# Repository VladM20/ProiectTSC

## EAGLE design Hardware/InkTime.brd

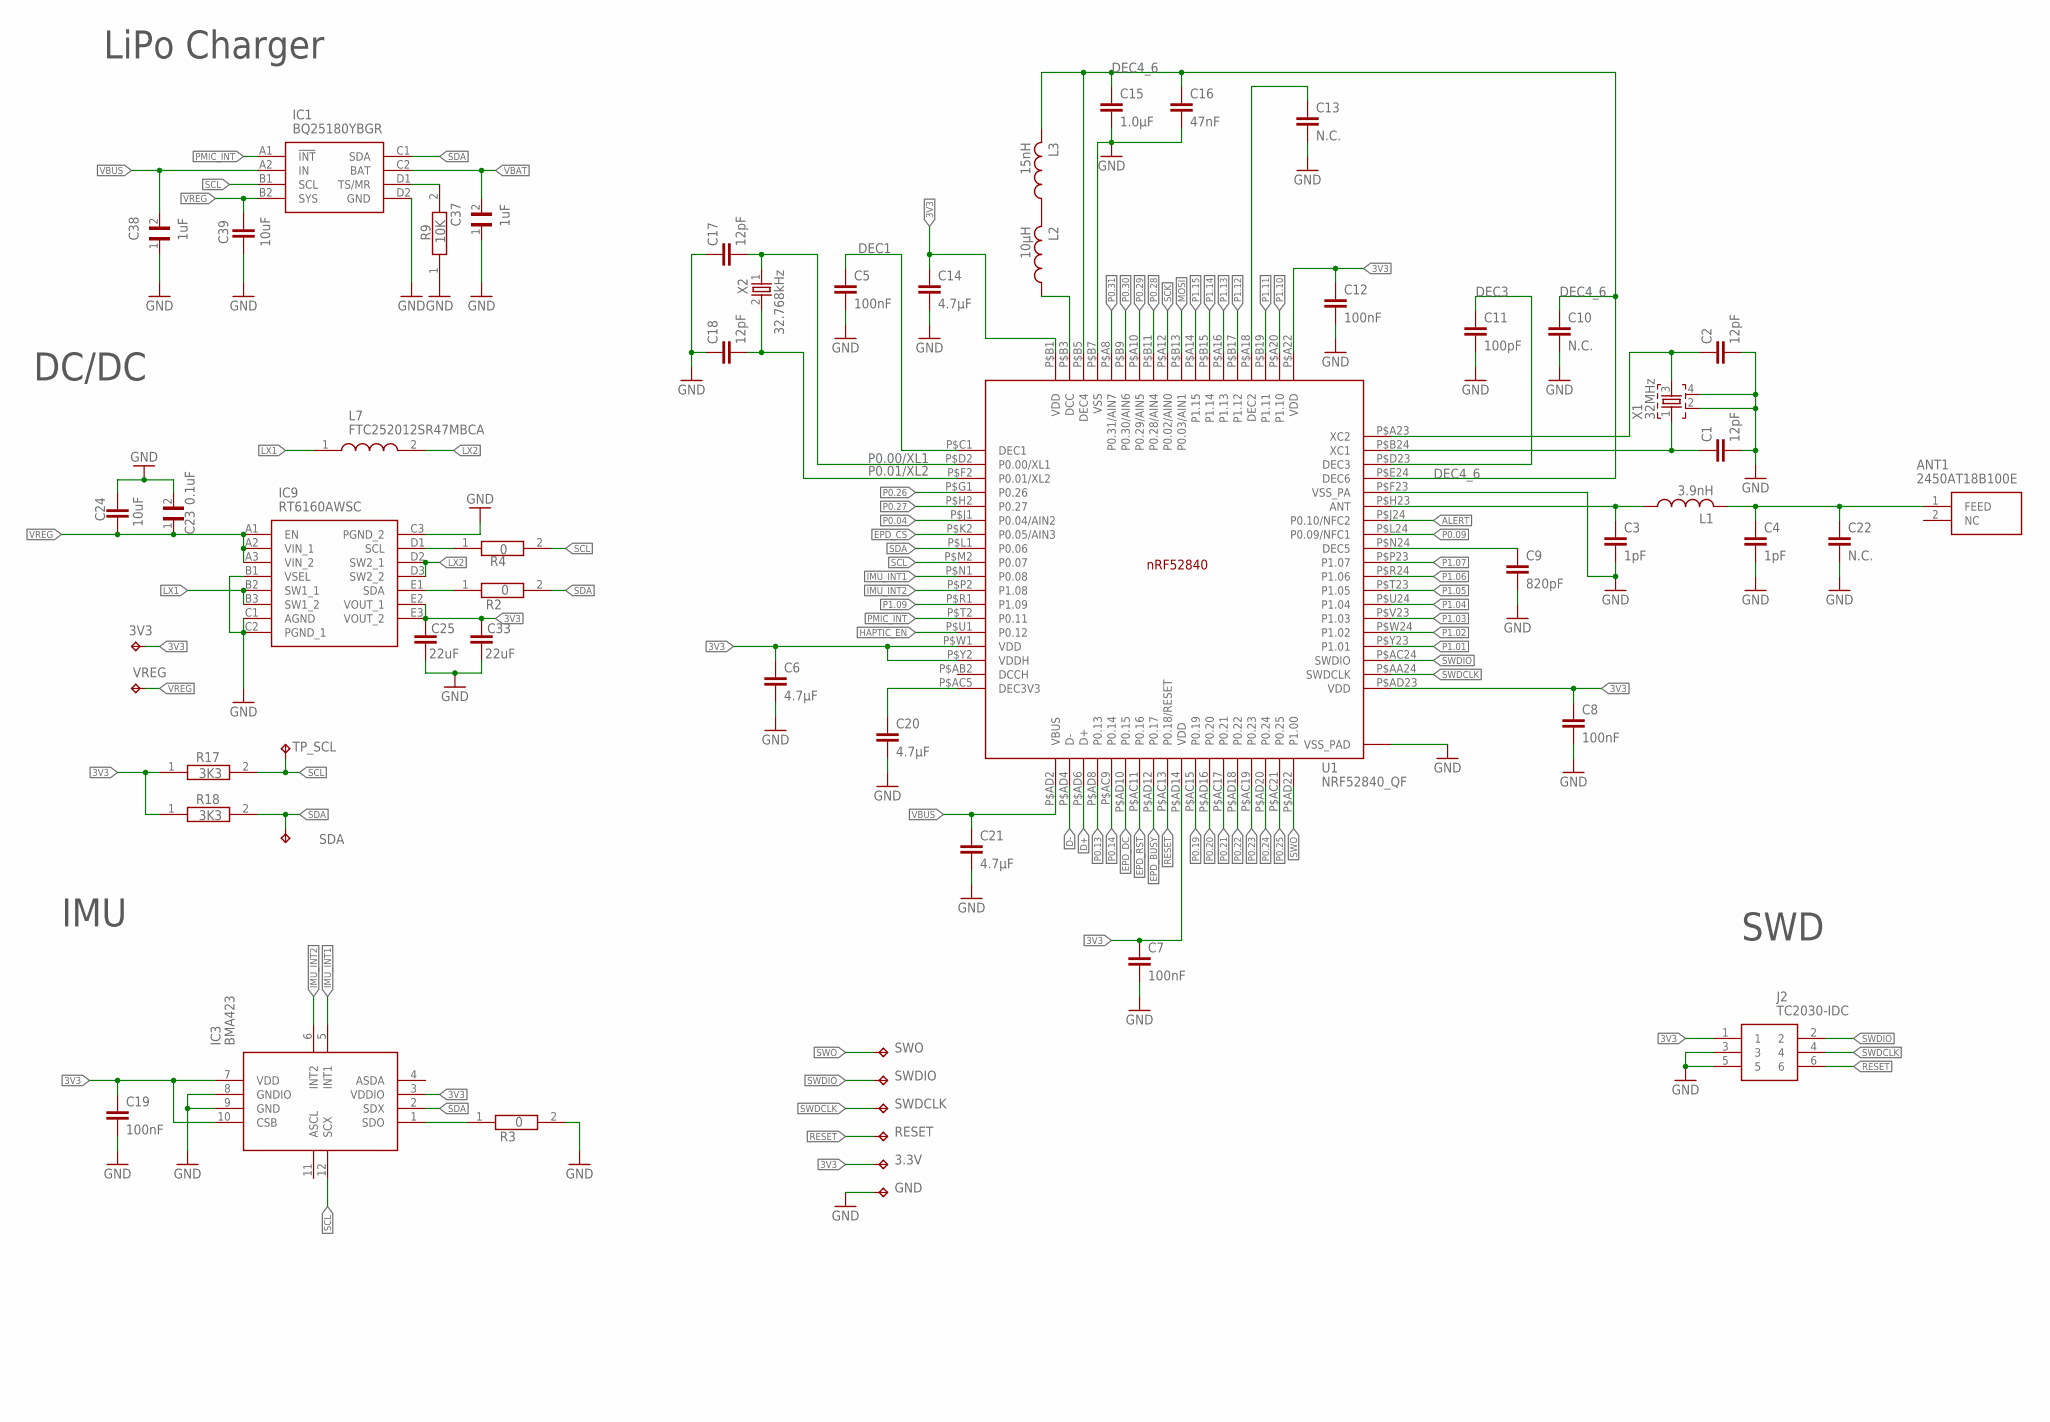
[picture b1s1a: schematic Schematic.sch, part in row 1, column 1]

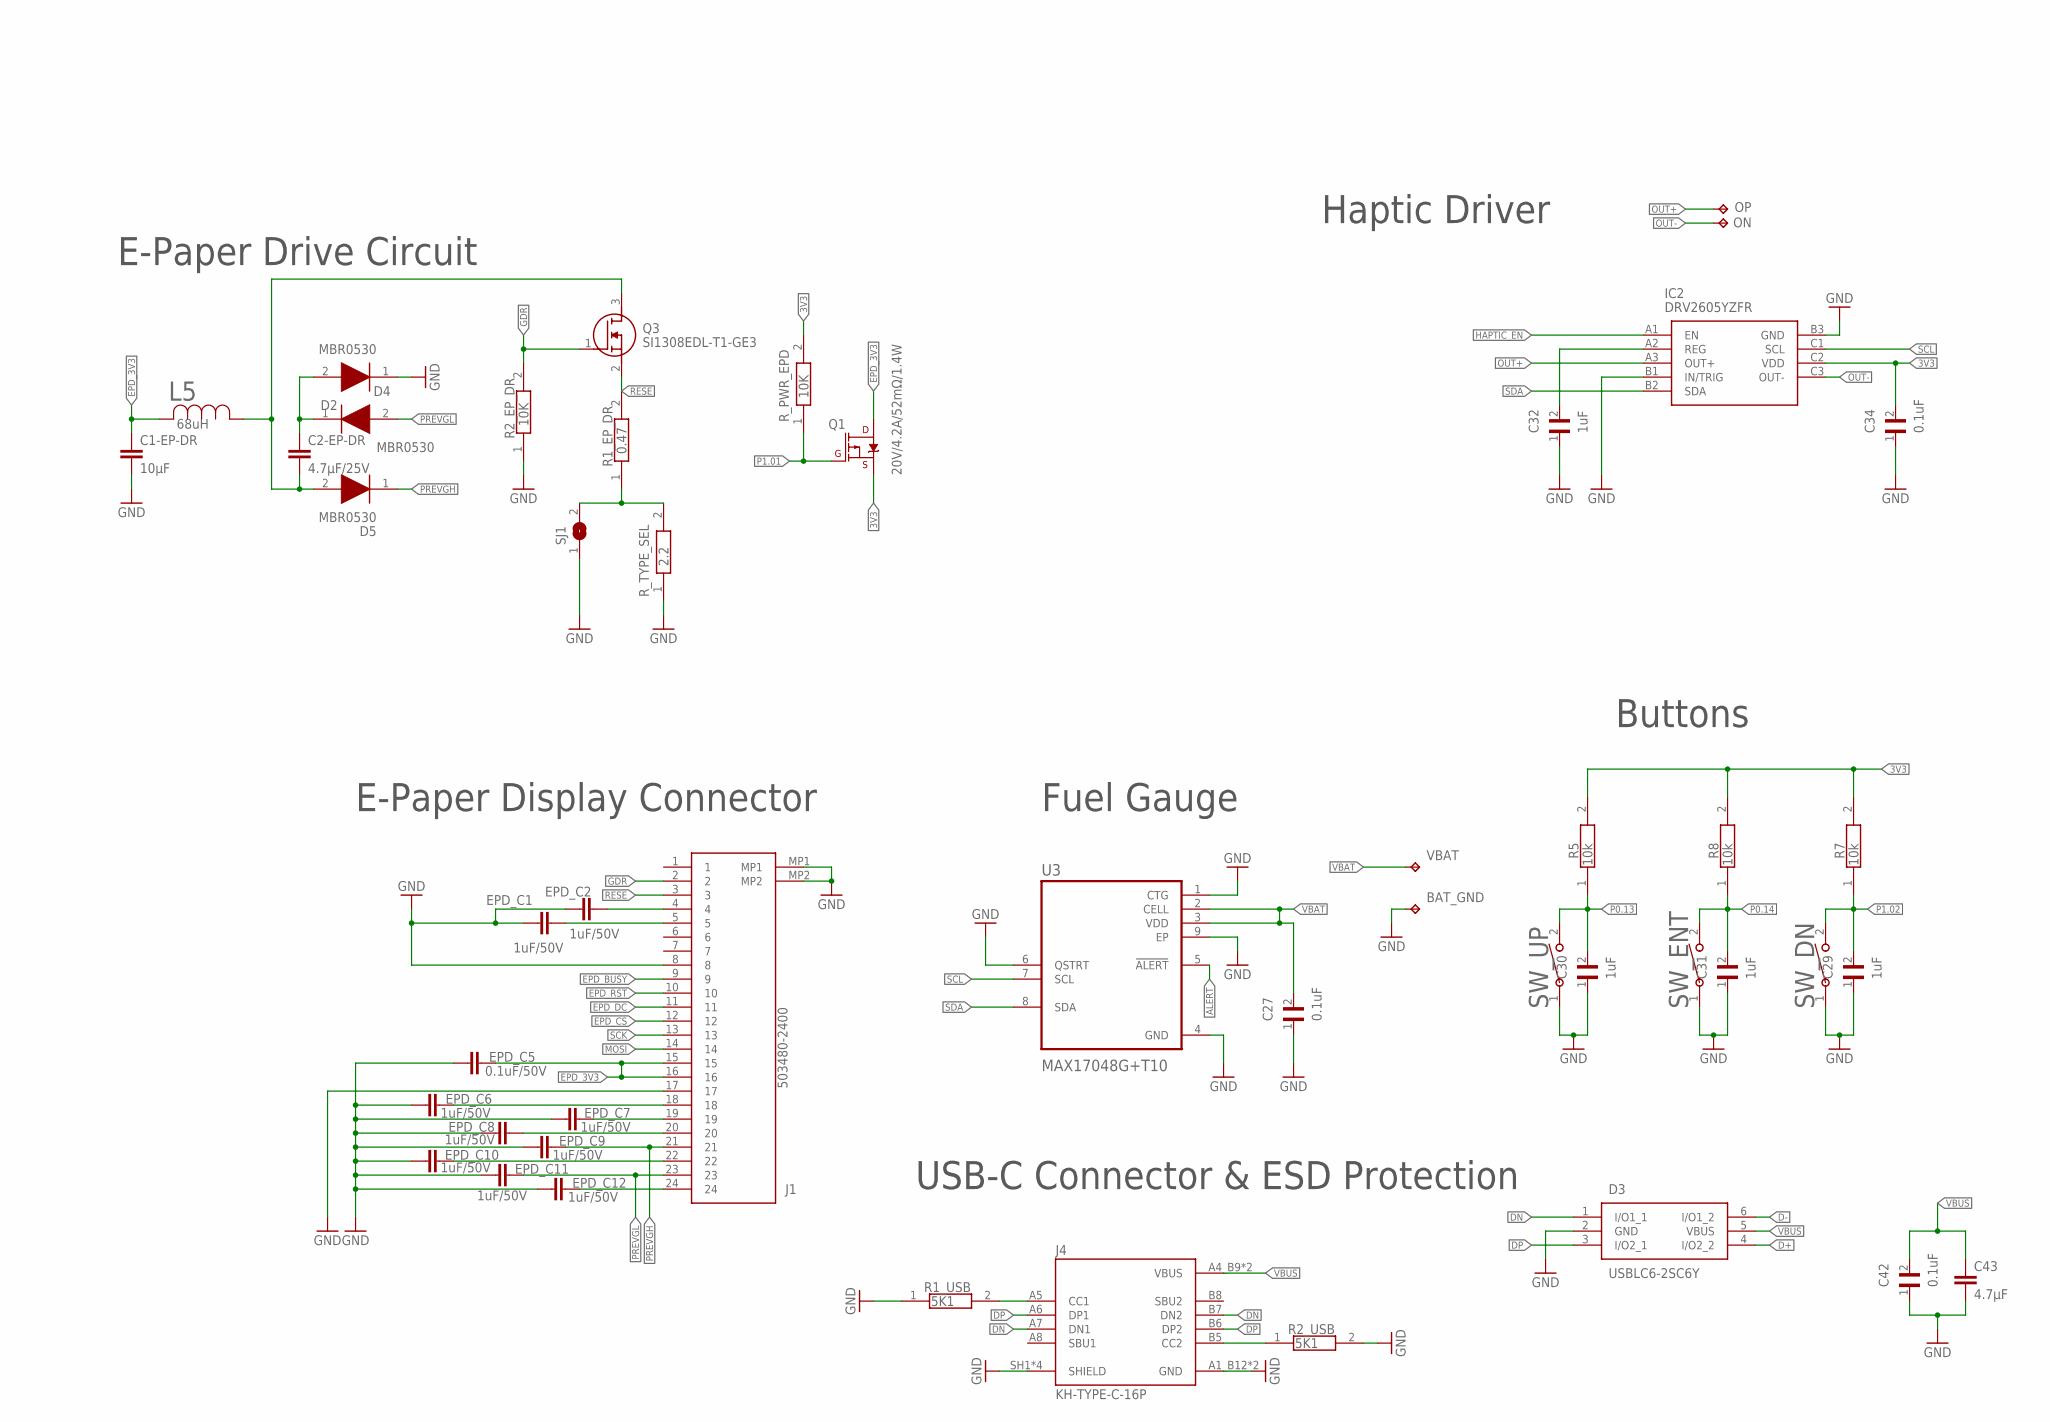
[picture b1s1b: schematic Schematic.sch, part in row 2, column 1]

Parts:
3.3V, 3V3: HECTOR_WATCH_1_TPTP20R; HECTOR_WATCH_1_TP20R
ANT1: 2450AT18B100E; 2450AT18B100E_ANTC3216X140N
BAT_GND: HECTOR_WATCH_1_TPTP20R; HECTOR_WATCH_1_TP20R
C1, C2, C17, C18: 12pF; GRM011R60J152KE01L_2_CAPC0201X13N
C1-EP-DR: 10μF; NORDIC_NRF_2_RESC0402_L
C2-EP-DR: 4.7μF/25V; NORDIC_NRF_2_RESC0402_L
C3, C4: 1pF; GRM011R60J152KE01L_2_CAPC0201X13N
C5, C7, C8, C12, C19: 100nF; GRM011R60J152KE01L_2_CAPC0201X13N
C6, C14, C20, C21, C43: 4.7μF; NORDIC_NRF_2_RESC0402_L
C9: 820pF; GRM011R60J152KE01L_2_CAPC0201X13N
C10, C13, C22: N.C.; GRM011R60J152KE01L_2_CAPC0201X13N
C11: 100pF; GRM011R60J152KE01L_2_CAPC0201X13N
C15: 1.0μF; NORDIC_NRF_2_RESC0402_L
C16: 47nF; GRM011R60J152KE01L_2_CAPC0201X13N
C23, C27, C34, C42: 0.1uF; GRM011R60J152KE01L_2_CAPC0201X13N
C24: 10uF; PERFECT_0402_0402
C25, C33: 22uF; PERFECT_0402_0402
C29, C30, C31, C32, C37, C38: 1uF; GRM011R60J152KE01L_2_CAPC0201X13N
C39: 10uF; NORDIC_NRF_2_RESC0402_L
D2, D4, D5: MBR0530; ESP32_C6_LIBRARY_5_SOD3716X135N
D3: USBLC6-2SC6Y; ESP32_C6_LIBRARY_3_SOT95P280X145-6N
EPD_C1, EPD_C2, EPD_C6, EPD_C7, EPD_C8, EPD_C9, EPD_C10, EPD_C11, EPD_C12: 1uF/50V; GRM011R60J152KE01L_2_CAPC0201X13N
EPD_C5: 0.1uF/50V; GRM011R60J152KE01L_2_CAPC0201X13N
GND: HECTOR_WATCH_1_TPTP20R; HECTOR_WATCH_1_TP20R
IC1: BQ25180YBGR; BQ25180YBGR_BGA8C40P2X4_100X155X50
IC2: DRV2605YZFR; DRV2605YZFR_BGA9C50P3X3_144X144X62
IC3: BMA423; BMA423_BMA423
IC9: RT6160AWSC; RT6160AWSC_BGA15C40P3X5_140X230X60
J1: 503480-2400; 503480-2400_5034802400
J2: TC2030-IDC; TC2030-IDC_TC2030IDC
J4: KH-TYPE-C-16P; KH-TYPE-C-16P_KINGHELM_KH-TYPE-C-16P
L1: 3.9nH; NORDIC_NRF_2_RESC0201_L
L2: 10μH; NORDIC_NRF_2_RESC0201_L
L3: 15nH; NORDIC_NRF_2_RESC0201_L
L5: 68uH; ESP32_C6_LIBRARY_2_IND_4828-WE-TPC_WRE
L7: FTC252012SR47MBCA; MLP2016SR47MT0S1_INDC2016X100N
ON: HECTOR_WATCH_1_TPTP20R; HECTOR_WATCH_1_TP20R
OP: HECTOR_WATCH_1_TPTP20R; HECTOR_WATCH_1_TP20R
Q1: 20V/4.2A/52mΩ/1.4W; ESP32_C6_LIBRARY_4_ESP32_C6_LIBRARY_4_ESP32_C6_LIBRARY_4_ES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
Q3: SI1308EDL-T1-GE3; ESP32_C6_LIBRARY_6_SOT65P210X110-3N
R1_EP_DR: 0.47; ERA-1AEB3401C_0201
R1_USB, R2_USB: 5K1; ERA-1AEB3401C_0201
R2, R3, R4: 0; ERA-1AEB3401C_0201
R2_EP_DR, R9: 10K; ERA-1AEB3401C_0201
R5, R7, R8: 10k; ERA-1AEB3401C_0201
R17, R18: 3K3; ERA-1AEB3401C_0201
RESET: HECTOR_WATCH_1_TPTP20R; HECTOR_WATCH_1_TP20R
R_PWR_EPD: 10K; ERA-1AEB3401C_0201
R_TYPE_SEL: 2.2; ERA-1AEB3401C_0201
SDA: HECTOR_WATCH_1_TPTP20R; HECTOR_WATCH_1_TP20R
SJ1: ESP32_C6_LIBRARY_7_JUMPER_SJ
SWDCLK: HECTOR_WATCH_1_TPTP20R; HECTOR_WATCH_1_TP20R
SWDIO: HECTOR_WATCH_1_TPTP20R; HECTOR_WATCH_1_TP20R
SWO: HECTOR_WATCH_1_TPTP20R; HECTOR_WATCH_1_TP20R
SW_DN: 2025-10-22_07-23-44_LIBRARY_EVP-AKE31ASW_EVP-AKE3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; 2025-10-22_07-23-44_LIBRARY_SW_EVP-AKE31A_PAN
SW_ENT: 2025-10-22_07-23-44_LIBRARY_EVP-AKE31ASW_EVP-AKE3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; 2025-10-22_07-23-44_LIBRARY_SW_EVP-AKE31A_PAN
SW_UP: 2025-10-22_07-23-44_LIBRARY_EVP-AKE31ASW_EVP-AKE3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; 2025-10-22_07-23-44_LIBRARY_SW_EVP-AKE31A_PAN
TP_SCL: HECTOR_WATCH_1_TPTP20R; HECTOR_WATCH_1_TP20R
U1: NRF52840_QF; NORDIC_NRF_4_AQFN50P700X700X85_HS-74N
U3: MAX17048G+T10; ESP32_C6_LIBRARY_SON50P200X200X80-9N
VBAT: HECTOR_WATCH_1_TPTP20R; HECTOR_WATCH_1_TP20R
VREG: HECTOR_WATCH_1_TPTP20R; HECTOR_WATCH_1_TP20R
X1: 32MHz; NORDIC_NRF_BT-XTAL_2016_N
X2: 32.768kHz; NORDIC_NRF_BT-XTAL_2016_N

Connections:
3V3: 3.3V.TP, 3V3.TP, C6.1, C7.1, C8.1, C12.1, C14.1, C19.1, C25.2, C33.2, C34.2, IC2.C2 (VDD), IC3.3 (VDDIO), IC3.7 (VDD), IC3.10 (CSB), IC9.E2 (VOUT_1), IC9.E3 (VOUT_2), J2.1, Q1.2 (S), R5.2, R7.2, R8.2, R17.1, R18.1, R_PWR_EPD.2, U1.P$A22 (VDD), U1.P$AD14 (VDD), U1.P$AD23 (VDD), U1.P$B1 (VDD), U1.P$W1 (VDD), U1.P$Y2 (VDDH)
3V3/2.4A1: C9.1, U1.P$N24 (DEC5)
ALERT: U1.P$J24 (P0.10/NFC2), U3.5 (!ALERT)
D+: D3.4 (I/O2_2), U1.P$AD6 (D+)
D-: D3.6 (I/O1_2), U1.P$AD4 (D-)
DEC1: C5.1, U1.P$C1 (DEC1)
DEC2: C3.1, L1.1, U1.P$H23 (ANT)
DEC3: C11.1, U1.P$D23 (DEC3)
DEC4: ANT1.1 (FEED), C4.1, C22.1, L1.2
DEC4_6: C10.1, C15.1, C16.1, L3.2, U1.P$B5 (DEC4), U1.P$E24 (DEC6)
DN: D3.1 (I/O1_1), J4.A7 (DN1), J4.B7 (DN2)
DP: D3.3 (I/O2_1), J4.A6 (DP1), J4.B6 (DP2)
EPD_3V3: C1-EP-DR.1, EPD_C5.2, J1.15, J1.16, L5.2, Q1.3 (D)
EPD_BUSY: J1.9, U1.P$AD12 (P0.17)
EPD_CS: J1.12, U1.P$K2 (P0.05/AIN3)
EPD_DC: J1.11, U1.P$AD10 (P0.15)
EPD_RST: J1.10, U1.P$AC11 (P0.16)
GDR: J1.2, Q3.1 (G), R2_EP_DR.2
GND: BAT_GND.TP, C1.2, C1-EP-DR.2, C2.2, C3.2, C4.2, C5.2, C6.2, C7.2, C8.2, C9.2, C10.2, C11.2, C12.2, C13.2, C14.2, C15.2, C16.2, C17.1, C18.1, C19.2, C20.2, C21.2, C22.2, C23.2, C24.1, C25.1, C27.1, C29.1, C30.1, C31.1, C32.1, C33.1, C34.1, C37.1, C38.1, C39.2, C42.1, C43.2, D3.2 (GND), D4.1 (K), EPD_C1.1, EPD_C2.1, EPD_C5.1, EPD_C6.1, EPD_C7.1, EPD_C8.1, EPD_C9.1, EPD_C10.1, EPD_C11.1, EPD_C12.1, GND.TP, IC1.D2 (GND), IC2.B1 (IN/TRIG), IC2.B3 (GND), IC3.8 (GNDIO), IC3.9 (GND), IC9.B1 (VSEL), IC9.C1 (AGND), IC9.C2 (PGND_1), IC9.C3 (PGND_2), J1.8, J1.17, J1.MP1, J1.MP2, J2.3, J2.5, J4.A1_B12 (GND), J4.A12_B1 (GND), J4.SH1 (SHIELD), J4.SH2 (SHIELD), J4.SH3 (SHIELD), J4.SH4 (SHIELD), R1_USB.1, R2_EP_DR.1, R2_USB.2, R3.2, R9.1, R_TYPE_SEL.1, SJ1.1, SW_DN.1, SW_ENT.1, SW_UP.1, U1.P$74 (VSS_PAD), U1.P$75 (VSS_PAD), U1.P$76 (VSS_PAD), U1.P$77 (VSS_PAD), U1.P$78 (VSS_PAD), U1.P$79 (VSS_PAD), U1.P$80 (VSS_PAD), U1.P$81 (VSS_PAD), U1.P$82 (VSS_PAD), U1.P$83 (VSS_PAD), U1.P$84 (VSS_PAD), U1.P$85 (VSS_PAD), U1.P$86 (VSS_PAD), U1.P$87 (VSS_PAD), U1.P$88 (VSS_PAD), U1.P$89 (VSS_PAD), U1.P$90 (VSS_PAD), U1.P$B7 (VSS), U1.P$F23 (VSS_PA), U3.1 (CTG), U3.4 (GND), U3.6 (QSTRT), U3.9 (EP), X1.2, X1.4
HAPTIC_EN: IC2.A1 (EN), U1.P$U1 (P0.12)
IMU_INT1: IC3.5 (INT1), U1.P$N1 (P0.08)
IMU_INT2: IC3.6 (INT2), U1.P$P2 (P1.08)
LX1: IC9.B2 (SW1_1), IC9.B3 (SW1_2), L7.1
LX2: IC9.D2 (SW2_1), IC9.D3 (SW2_2), L7.2
MOSI: J1.14, U1.P$B13 (P0.03/AIN1)
unnamed: IC9.D1 (SCL), R4.1
unnamed: IC9.E1 (SDA), R2.1
unnamed: L2.2, L3.1
unnamed: C2-EP-DR.2, D5.2 (A), L5.1, Q3.3 (D)
unnamed: C1.1, U1.P$B24 (XC1), X1.1
unnamed: C2-EP-DR.1, D2.1 (K), D4.2 (A)
unnamed: R1_EP_DR.1, R_TYPE_SEL.2, SJ1.2
unnamed: IC3.1 (SDO), R3.1
unnamed: EPD_C12.2, J1.24
unnamed: C13.1, U1.P$A18 (DEC2)
unnamed: EPD_C2.2, J1.4
unnamed: EPD_C1.2, J1.5
unnamed: C32.2, IC2.A2 (REG)
unnamed: J4.B5 (CC2), R2_USB.1
unnamed: J4.A5 (CC1), R1_USB.2
unnamed: C20.1, U1.P$AC5 (DEC3V3)
unnamed: EPD_C6.2, J1.18
unnamed: EPD_C7.2, J1.19
unnamed: EPD_C8.2, J1.20
unnamed: EPD_C10.2, J1.22
unnamed: C2.1, U1.P$A23 (XC2), X1.3
unnamed: L2.1, U1.P$B3 (DCC)
OUT+: IC2.A3 (OUT+), OP.TP
OUT-: IC2.C3 (OUT-), ON.TP
P0.00/XL1: C17.2, U1.P$D2 (P0.00/XL1), X2.1
P0.01/XL2: C18.2, U1.P$F2 (P0.01/XL2), X2.2
P0.04: U1.P$J1 (P0.04/AIN2)
P0.09: U1.P$L24 (P0.09/NFC1)
P0.13: C30.2, R5.1, SW_UP.2, U1.P$AD8 (P0.13)
P0.14: C31.2, R8.1, SW_ENT.2, U1.P$AC9 (P0.14)
P0.19: U1.P$AC15 (P0.19)
P0.20: U1.P$AD16 (P0.20)
P0.21: U1.P$AC17 (P0.21)
P0.22: U1.P$AD18 (P0.22)
P0.23: U1.P$AC19 (P0.23)
P0.24: U1.P$AD20 (P0.24)
P0.25: U1.P$AC21 (P0.25)
P0.26: U1.P$G1 (P0.26)
P0.27: U1.P$H2 (P0.27)
P0.28: U1.P$B11 (P0.28/AIN4)
P0.29: U1.P$A10 (P0.29/AIN5)
P0.30: U1.P$B9 (P0.30/AIN6)
P0.31: U1.P$A8 (P0.31/AIN7)
P1.01: Q1.1 (G), R_PWR_EPD.1, U1.P$Y23 (P1.01)
P1.02: C29.2, R7.1, SW_DN.2, U1.P$W24 (P1.02)
P1.03: U1.P$V23 (P1.03)
P1.04: U1.P$U24 (P1.04)
P1.05: U1.P$T23 (P1.05)
P1.06: U1.P$R24 (P1.06)
P1.07: U1.P$P23 (P1.07)
P1.09: U1.P$R1 (P1.09)
P1.10: U1.P$A20 (P1.10)
P1.11: U1.P$B19 (P1.11)
P1.12: U1.P$B17 (P1.12)
P1.13: U1.P$A16 (P1.13)
P1.14: U1.P$B15 (P1.14)
P1.15: U1.P$A14 (P1.15)
PMIC_INT: IC1.A1 (!INT), U1.P$T2 (P0.11)
PREVGH: D5.1 (K), EPD_C9.2, J1.21
PREVGL: D2.2 (A), EPD_C11.2, J1.23
RESE: J1.3, Q3.2 (S), R1_EP_DR.2
RESET: J2.6, RESET.TP, U1.P$AC13 (P0.18/RESET)
SCK: J1.13, U1.P$A12 (P0.02/AIN0)
SCL: IC1.B1 (SCL), IC2.C1 (SCL), IC3.12 (SCX), R4.2, R17.2, TP_SCL.TP, U1.P$M2 (P0.07), U3.7 (SCL)
SDA: IC1.C1 (SDA), IC2.B2 (SDA), IC3.2 (SDX), R2.2, R18.2, SDA.TP, U1.P$L1 (P0.06), U3.8 (SDA)
SWDCLK: J2.4, SWDCLK.TP, U1.P$AA24 (SWDCLK)
SWDIO: J2.2, SWDIO.TP, U1.P$AC24 (SWDIO)
SWO: SWO.TP, U1.P$AD22 (P1.00)
TS/MR: IC1.D1 (TS/MR), R9.2
VBAT: C27.2, C37.2, IC1.C2 (BAT), U3.2 (CELL), U3.3 (VDD), VBAT.TP
VBUS: C21.1, C38.2, C42.2, C43.1, D3.5 (VBUS), IC1.A2 (IN), J4.A4_B9 (VBUS), J4.A9_B4 (VBUS), U1.P$AD2 (VBUS)
VREG: C23.1, C24.2, C39.1, IC1.B2 (SYS), IC9.A1 (EN), IC9.A2 (VIN_1), IC9.A3 (VIN_2), VREG.TP

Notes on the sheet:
LiPo Charger
DC/DC
IMU
SWD
E-Paper Drive Circuit
E-Paper Display Connector
Haptic Driver
Fuel Gauge
Buttons
USB-C Connector & ESD Protection

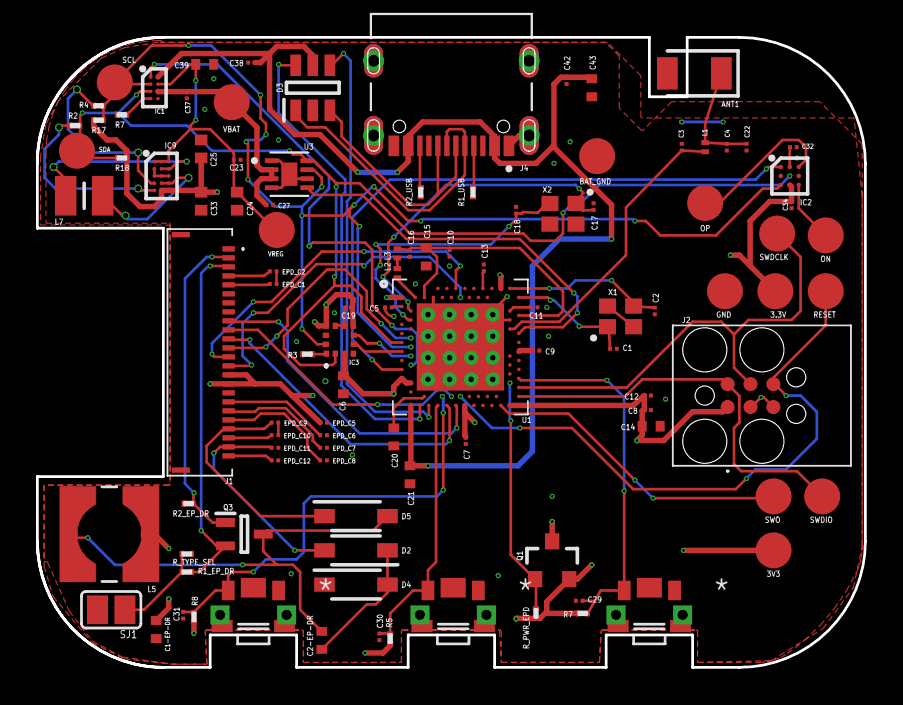
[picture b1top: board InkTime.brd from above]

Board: 4 copper layers, 46.0 x 35.0 mm, 105 parts (0 on the bottom side), 70 nets.

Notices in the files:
parts and their libraries:
COPYRIGHT: Copyright (C) 2024 Ultra Librarian. All rights reserved.
COPYRIGHT: Copyright (C) 2025 Ultra Librarian. All rights reserved.
